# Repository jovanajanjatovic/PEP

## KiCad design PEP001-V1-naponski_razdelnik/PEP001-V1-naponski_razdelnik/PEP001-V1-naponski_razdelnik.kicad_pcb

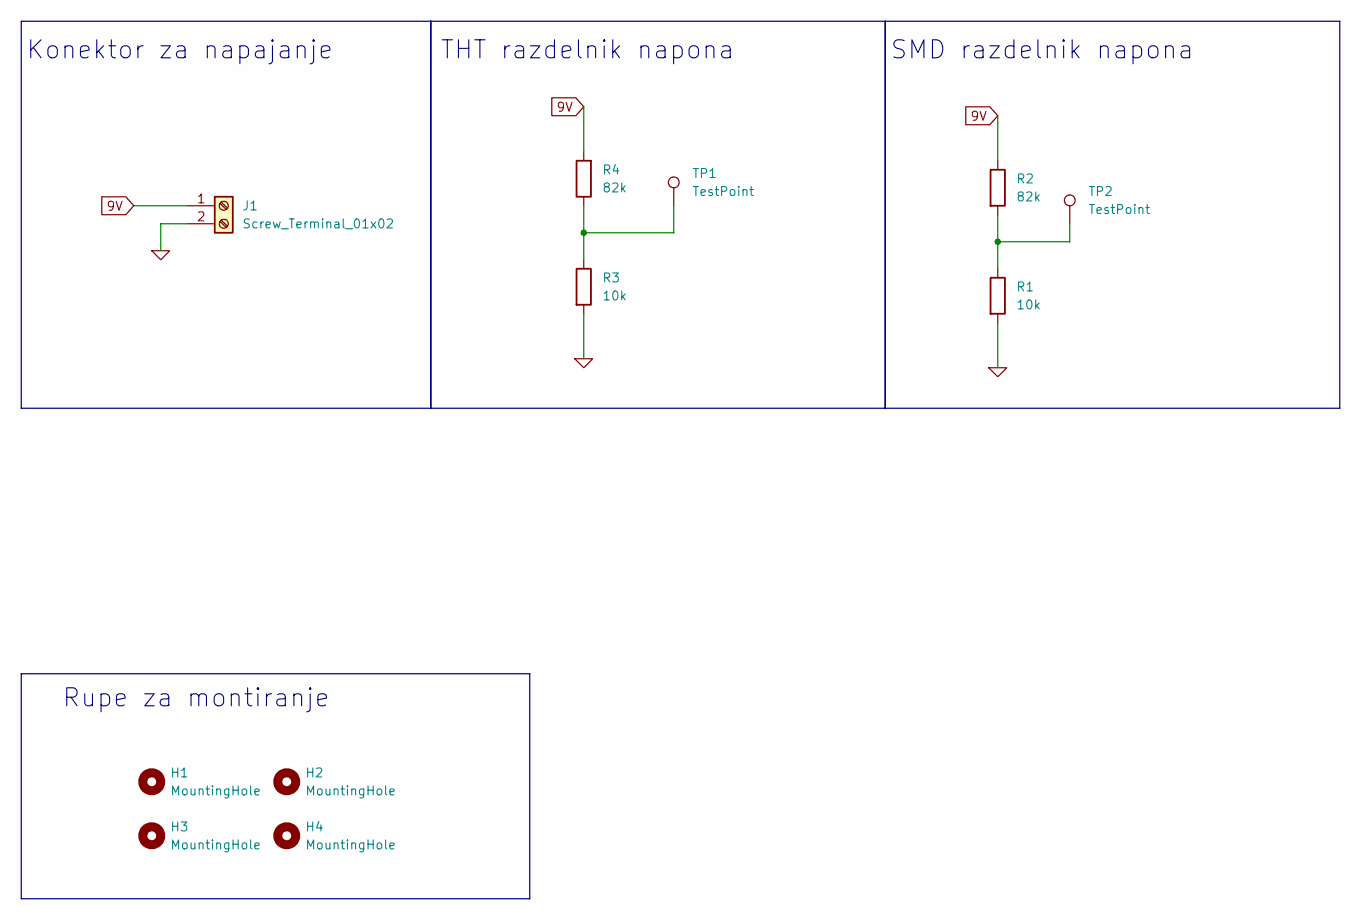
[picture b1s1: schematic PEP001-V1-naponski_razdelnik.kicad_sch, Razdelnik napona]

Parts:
H1, H2, H3, H4: MountingHole; MountingHole_3.2mm_M3_ISO14580_Pad_TopBottom
J1: Screw_Terminal_01x02; TerminalBlock_Phoenix_MKDS-1,5-2-5.08_1x02_P5.08mm_Horizont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; LCSC C3018698
R1: 10k; R_1206_3216Metric_Pad1.30x1.75mm_HandSolder; LCSC C17902
R2: 82k; R_1206_3216Metric_Pad1.30x1.75mm_HandSolder; LCSC C17979
R3: 10k; R_Axial_DIN0207_L6.3mm_D2.5mm_P15.24mm_Horizontal; LCSC C410695
R4: 82k; R_Axial_DIN0207_L6.3mm_D2.5mm_P15.24mm_Horizontal; LCSC C601724
TP1, TP2: TestPoint; TestPoint_Pad_D2.5mm

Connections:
0: J1.2, R1.2, R3.2
9V: J1.1, R2.1, R4.2
unnamed: R1.1, R2.2, TP2.1
unnamed: R3.1, R4.1, TP1.1

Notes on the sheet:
SMD razdelnik napona
Rupe za montiranje
Konektor za napajanje
THT razdelnik napona

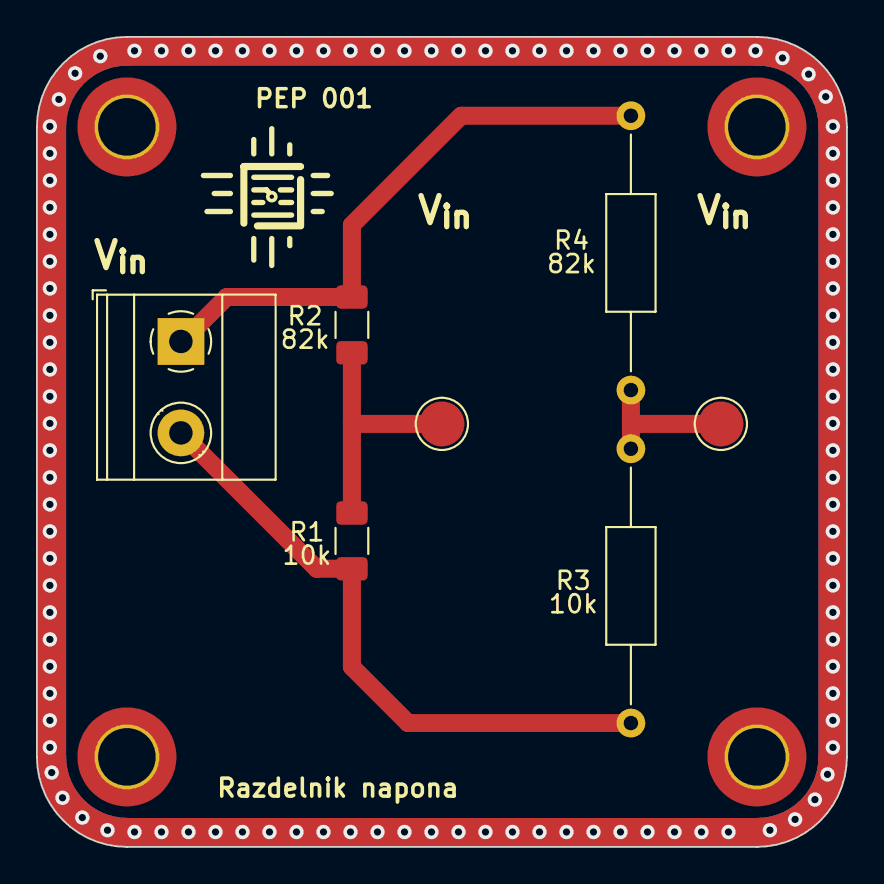
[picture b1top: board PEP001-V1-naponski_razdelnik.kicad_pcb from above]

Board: 2 copper layers, 45.0 x 45.0 mm, 11 parts (0 on the bottom side), 4 nets.

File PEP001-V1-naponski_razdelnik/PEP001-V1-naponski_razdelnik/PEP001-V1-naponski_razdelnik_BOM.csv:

"Comment","Designator","Footprint","LCSC Part Number"
"MountingHole,TestPoint","H1,H2,H3,H4,TP1,TP2","",""
"Screw_Terminal_01x02","J1","THT","C3018698"
"10k","R1","1206","C17902"
"82k","R2","1206","C17979"
"10k","R3","THT","C410695"
"82k","R4","THT","C601724"

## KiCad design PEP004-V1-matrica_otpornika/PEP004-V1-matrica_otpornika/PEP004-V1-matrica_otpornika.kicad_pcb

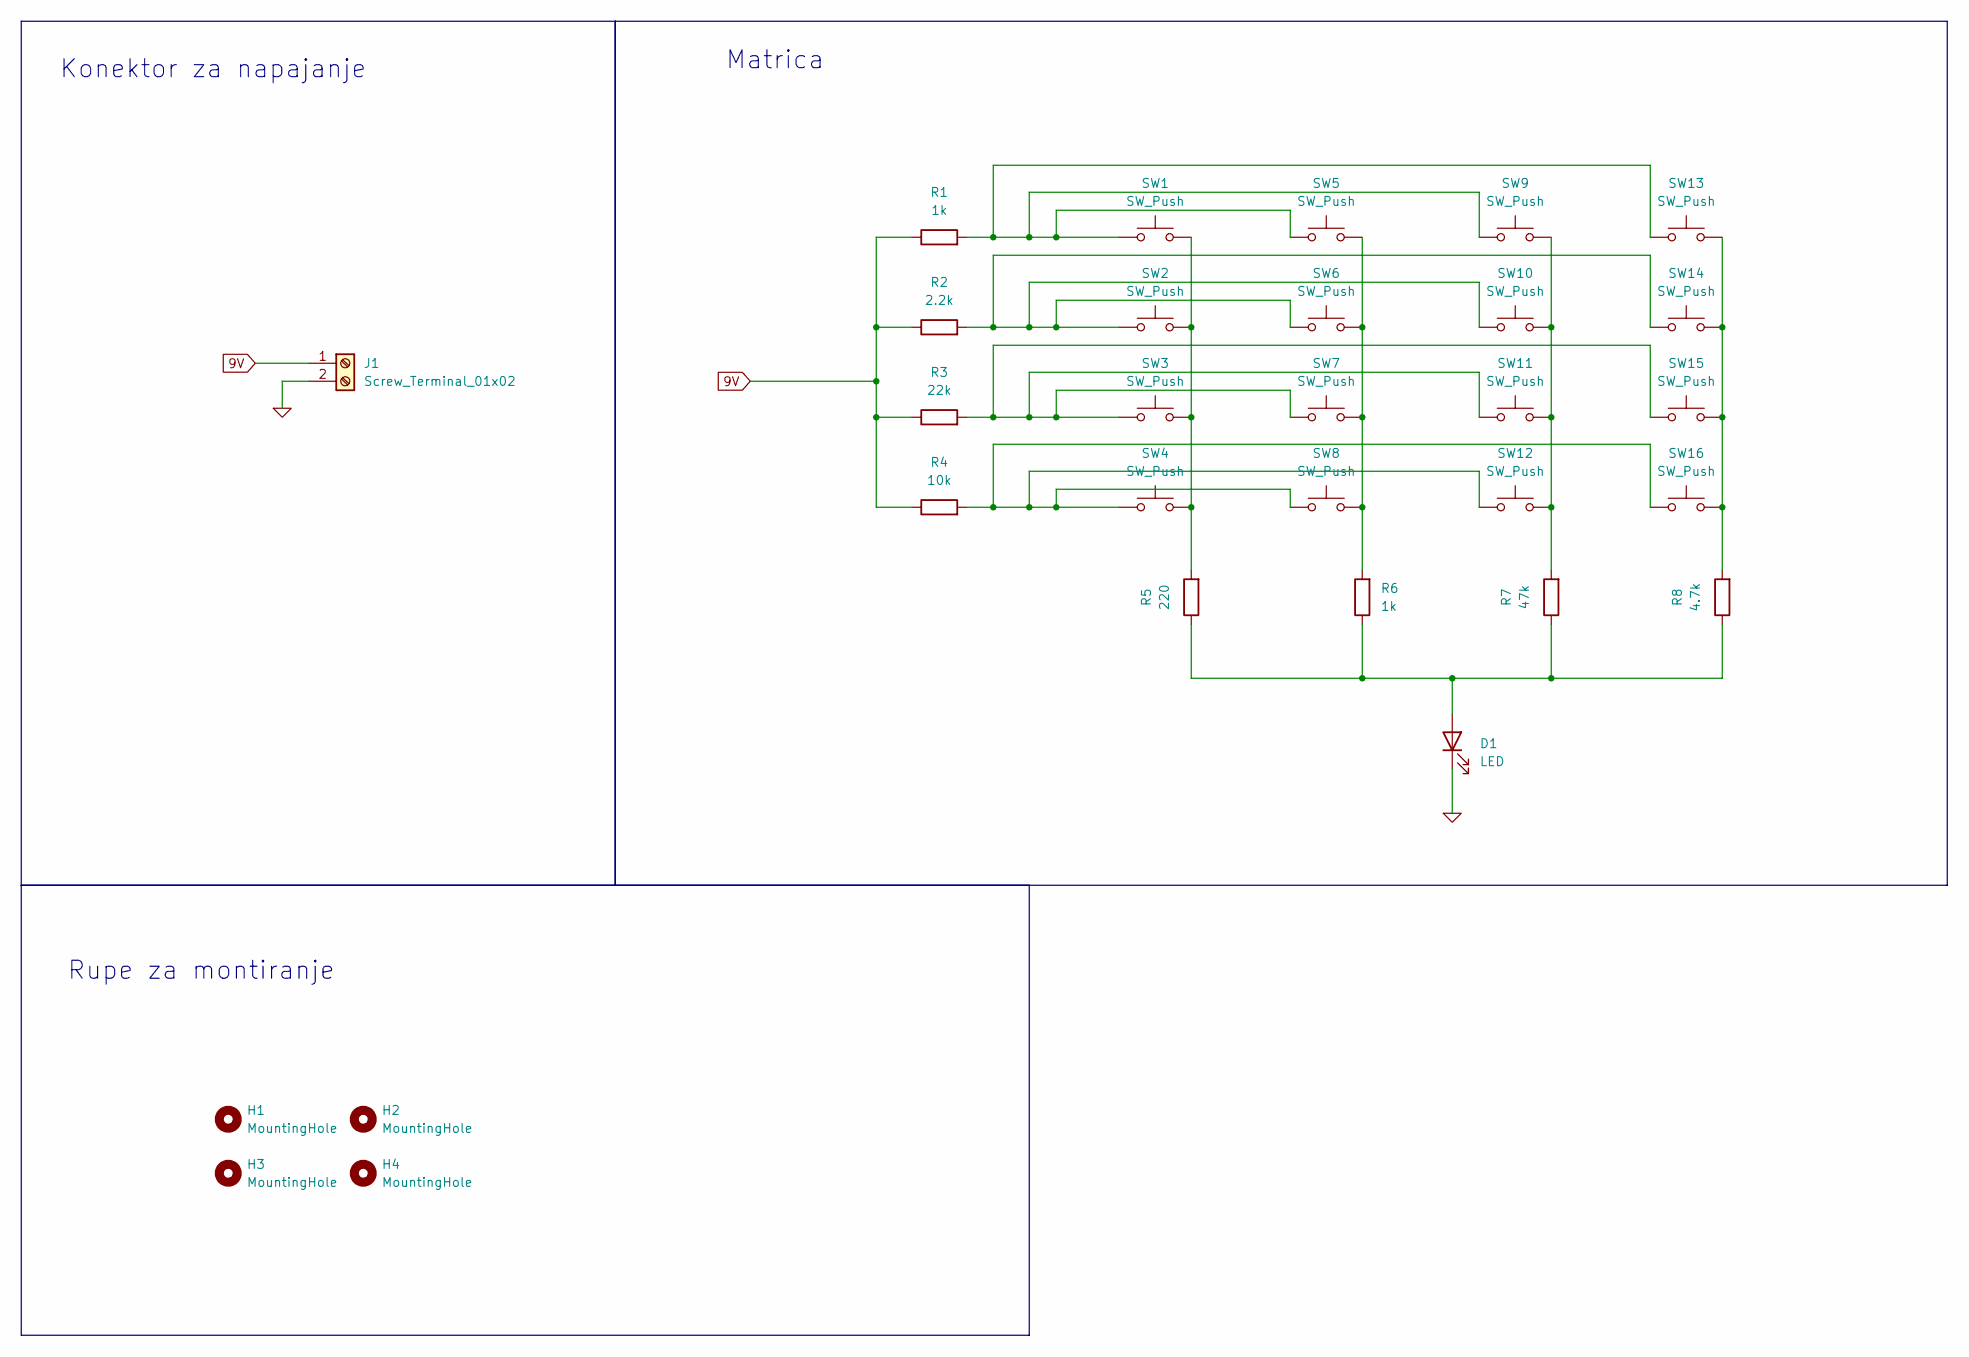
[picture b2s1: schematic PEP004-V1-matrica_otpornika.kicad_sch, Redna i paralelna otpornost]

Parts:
D1: LED; LED_0603_1608Metric_Pad1.05x0.95mm_HandSolder
H1, H2, H3, H4: MountingHole; MountingHole_3.2mm_M3_ISO14580_Pad_TopBottom
J1: Screw_Terminal_01x02; TerminalBlock_Phoenix_MKDS-1,5-2-5.08_1x02_P5.08mm_Horizont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
R1, R6: 1k; R_smd
R2: 2.2k; R_smd
R3: 22k; R_smd
R4: 10k; R_smd
R5: 220; R_smd
R7: 47k; R_smd
R8: 4.7k; R_smd
SW1, SW2, SW3, SW4, SW5, SW6, SW7, SW8, SW9, SW10, SW11, SW12, SW13, SW14, SW15, SW16: SW_Push; SW_PUSH_6mm_H4.3mm

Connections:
0: D1.1 (K), J1.2
9V: J1.1, R1.1, R2.1, R3.1, R4.1
unnamed: D1.2 (A), R5.1, R6.1, R7.1, R8.1
unnamed: R1.2, SW1.1, SW5.1, SW9.1, SW13.1
unnamed: R2.2, SW2.1, SW6.1, SW10.1, SW14.1
unnamed: R3.2, SW3.1, SW7.1, SW11.1, SW15.1
unnamed: R4.2, SW4.1, SW8.1, SW12.1, SW16.1
unnamed: R5.2, SW1.2, SW2.2, SW3.2, SW4.2
unnamed: R6.2, SW5.2, SW6.2, SW7.2, SW8.2
unnamed: R7.2, SW9.2, SW10.2, SW11.2, SW12.2
unnamed: R8.2, SW13.2, SW14.2, SW15.2, SW16.2

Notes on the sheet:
Konektor za napajanje
Rupe za montiranje
Matrica

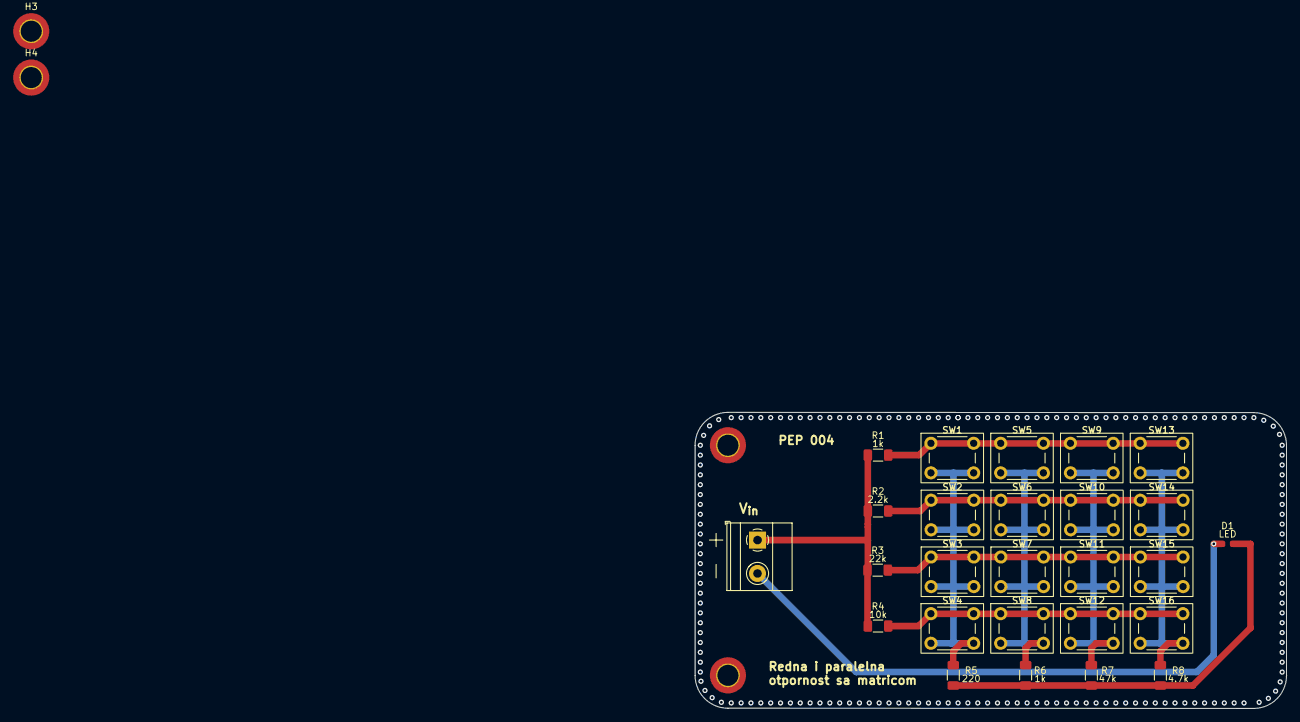
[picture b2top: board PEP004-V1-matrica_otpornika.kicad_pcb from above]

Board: 2 copper layers, 90.0 x 45.0 mm, 30 parts (0 on the bottom side), 11 nets.

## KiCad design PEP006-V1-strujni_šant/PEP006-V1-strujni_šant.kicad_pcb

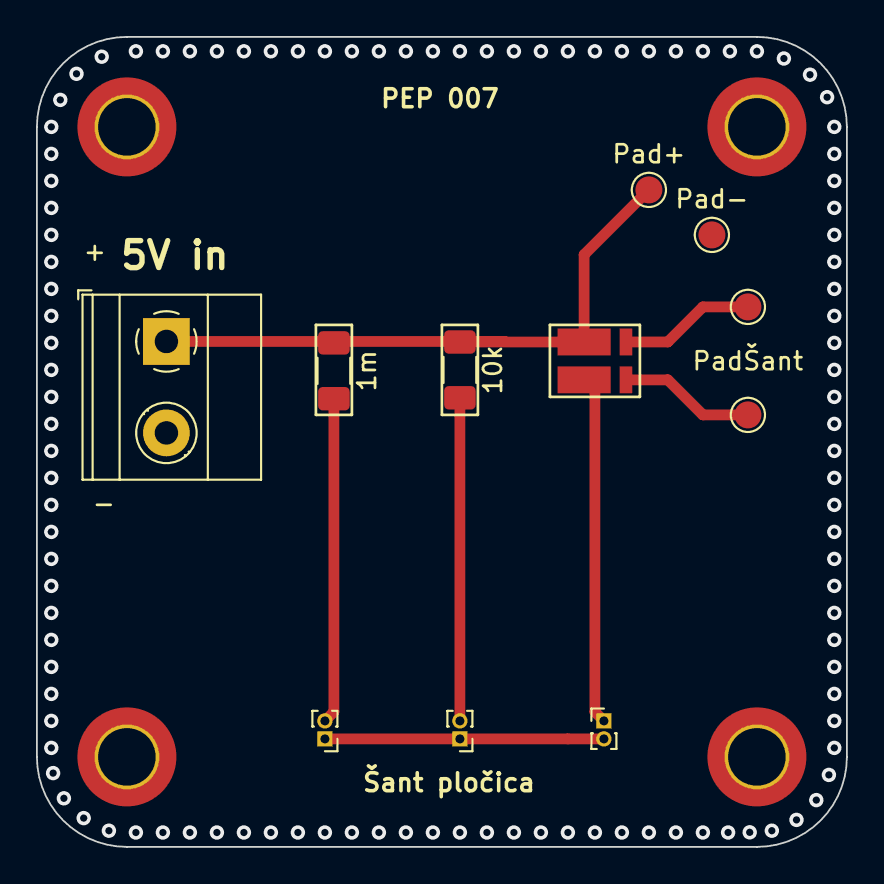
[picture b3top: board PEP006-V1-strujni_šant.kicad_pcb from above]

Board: 2 copper layers, 45.0 x 45.0 mm, 15 parts (0 on the bottom side), 7 nets.

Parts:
1m: 1m; R_1206_3216Metric_Pad1.30x1.75mm_HandSolder
10k: 10k; R_1206_3216Metric_Pad1.30x1.75mm_HandSolder
H1, H2, H3, H4: MountingHole; MountingHole_3.2mm_M3_ISO14580_Pad_TopBottom
J1: Screw_Terminal_01x02; TerminalBlock_Phoenix_MKDS-1,5-2-5.08_1x02_P5.08mm_Horizont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
J2, J3, J4: Conn_01x02_Pin; PinHeader_1x02_P1.00mm_Vertical
Pad+: TestPoint+; TestPoint_Pad_D1.5mm
Pad-: TestPoint-; TestPoint_Pad_D1.5mm
PadŠant: TestPointShunt; TestPoint_Pad_D1.5mm
R7: WSK12161; RES_WSK12161L000FEA
TP5: TestPointShunt; TestPoint_Pad_D1.5mm

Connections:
0: J1.2, J2.1, J3.1, J4.2, Pad-.1
unnamed: 1m.1, 10k.1, J1.1, Pad+.1, R7.2
unnamed: 1m.2, J2.2
unnamed: 10k.2, J3.2
unnamed: J4.1, R7.3
unnamed: R7.1, TP5.1
unnamed: PadŠant.1, R7.4

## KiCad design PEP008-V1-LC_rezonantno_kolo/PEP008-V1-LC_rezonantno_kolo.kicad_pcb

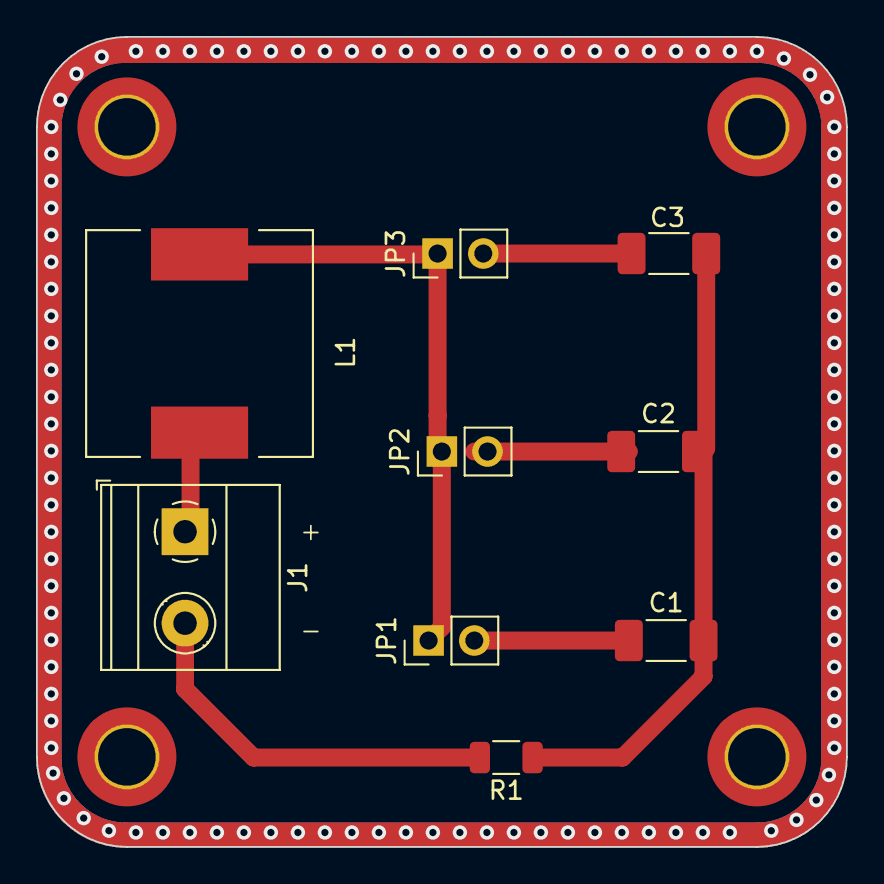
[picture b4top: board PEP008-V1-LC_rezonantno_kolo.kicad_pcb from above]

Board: 2 copper layers, 45.0 x 45.0 mm, 13 parts (0 on the bottom side), 7 nets.

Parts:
C1: 100n; C_1808_4520Metric
C2: 10n; C_1808_4520Metric
C3: 1n; C_1808_4520Metric
H1, H2, H3, H4: MountingHole; MountingHole_3.2mm_M3_ISO14580_Pad_TopBottom
J1: Screw_Terminal_01x02; TerminalBlock_Phoenix_MKDS-1,5-2-5.08_1x02_P5.08mm_Horizont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
JP1, JP2, JP3: Jumper; PinHeader_1x02_P2.54mm_Vertical
L1: 220µ; L_12x12mm_H4.5mm
R1: 100; R_1206_3216Metric

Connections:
GND: J1.2, R1.2
Input voltage: J1.1, L1.1
unnamed: C1.2, C2.2, C3.2, R1.1
unnamed: JP1.1 (A), JP2.1 (A), JP3.1 (A), L1.2
unnamed: C1.1, JP1.2 (B)
unnamed: C2.1, JP2.2 (B)
unnamed: C3.1, JP3.2 (B)

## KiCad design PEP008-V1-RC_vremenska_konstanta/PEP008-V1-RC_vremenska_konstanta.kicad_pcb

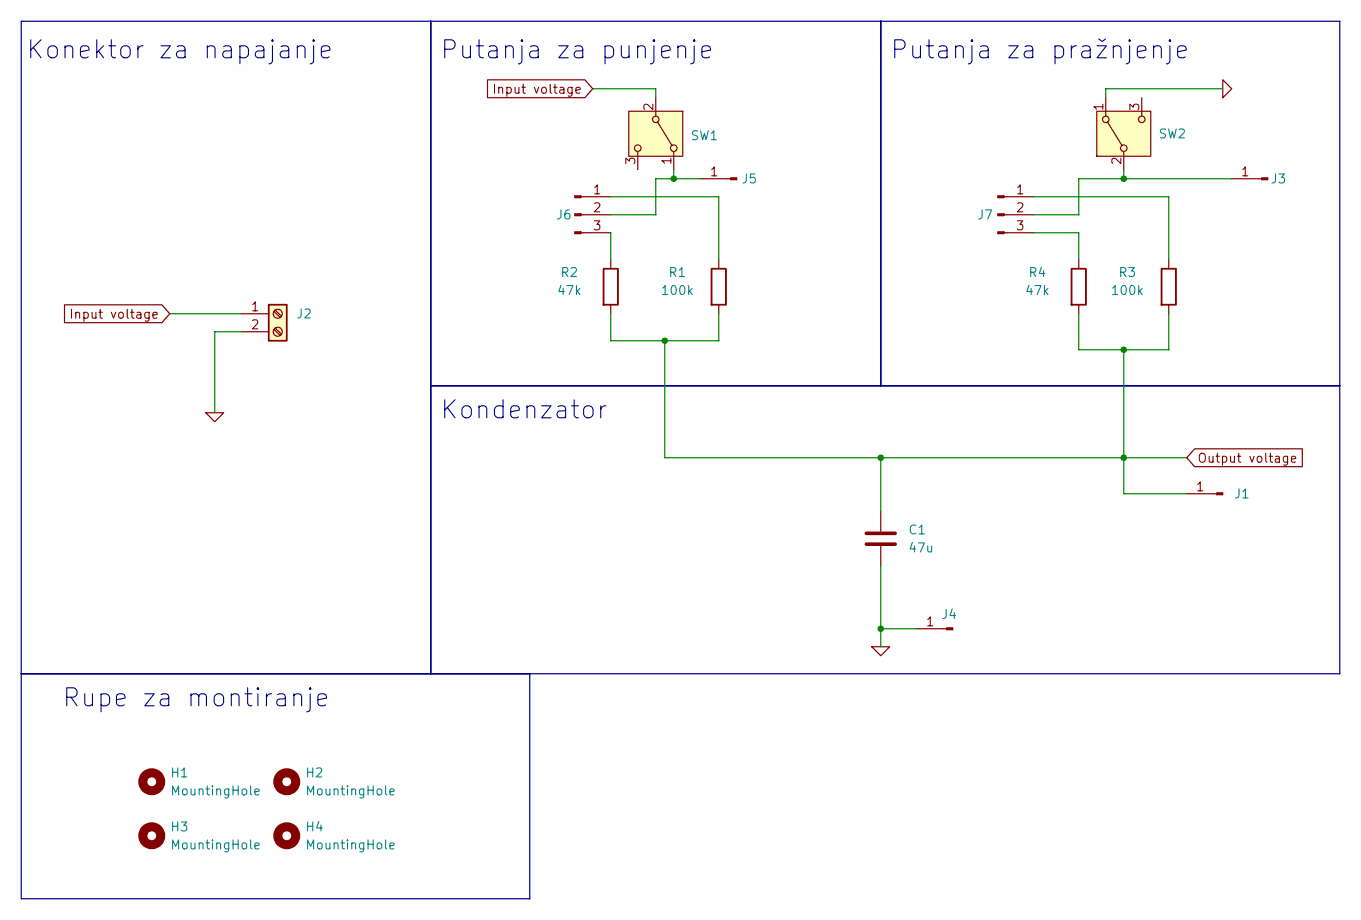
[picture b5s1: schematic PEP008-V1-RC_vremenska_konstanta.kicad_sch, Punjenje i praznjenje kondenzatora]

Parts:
C1: 47u; C_1206_3216Metric; LCSC C76659
H1, H2, H3, H4: MountingHole; MountingHole_3.2mm_M3_ISO14580_Pad_TopBottom
J1, J3, J4, J5: Conn_01x01_Pin; PinHeader_1x01_P2.54mm_Vertical
J2: Screw_Terminal_01x02; TerminalBlock_Phoenix_MKDS-1,5-2-5.08_1x02_P5.08mm_Horizont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
J6, J7: Conn_01x03_Pin; PinHeader_1x03_P2.54mm_Vertical
R1, R3: 100k; R_1206_3216Metric_Pad1.30x1.75mm_HandSolder; LCSC C17900
R2, R4: 47k; R_1206_3216Metric_Pad1.30x1.75mm_HandSolder; LCSC C25664
SW1, SW2: SW_SPDT; SW-TH_2MS1T1B1M1QES-5

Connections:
0: C1.2, J2.2, J4.1, SW2.1 (A)
Input voltage: J2.1, SW1.2 (B)
unnamed: J3.1, J7.2, SW2.2 (B)
unnamed: J5.1, J6.2, SW1.1 (A)
unnamed: J6.1, R1.1
unnamed: J6.3, R2.1
unnamed: J7.1, R3.1
unnamed: J7.3, R4.1
Output voltage: C1.1, J1.1, R1.2, R2.2, R3.2, R4.2

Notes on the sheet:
Rupe za montiranje
Kondenzator
Konektor za napajanje
Putanja za pražnjenje
Putanja za punjenje

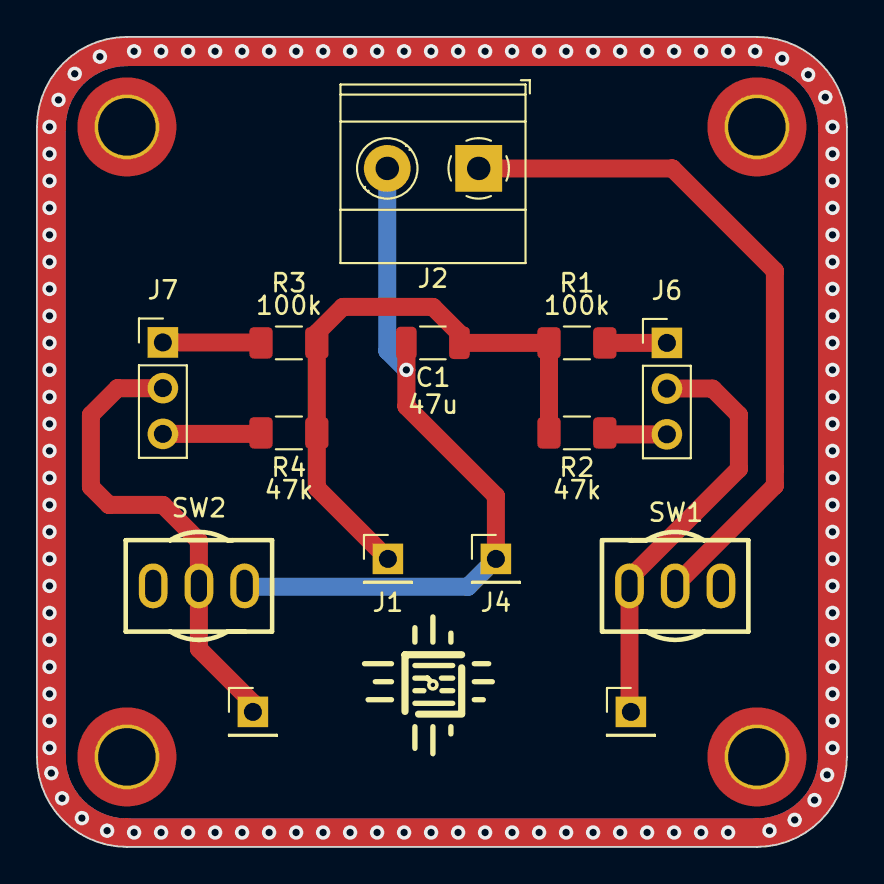
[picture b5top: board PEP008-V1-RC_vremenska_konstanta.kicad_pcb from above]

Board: 2 copper layers, 45.0 x 45.0 mm, 18 parts (0 on the bottom side), 9 nets.

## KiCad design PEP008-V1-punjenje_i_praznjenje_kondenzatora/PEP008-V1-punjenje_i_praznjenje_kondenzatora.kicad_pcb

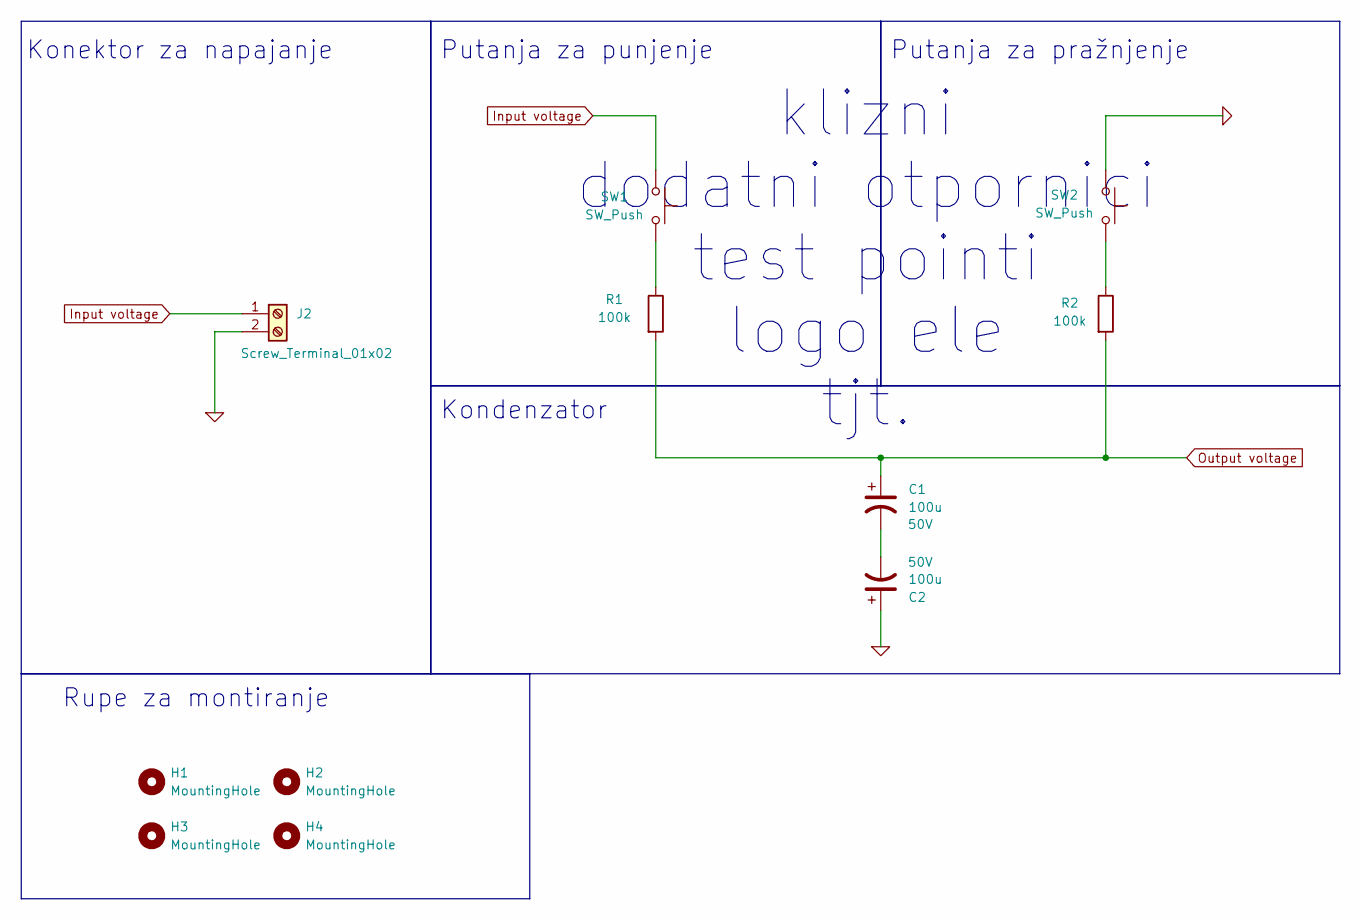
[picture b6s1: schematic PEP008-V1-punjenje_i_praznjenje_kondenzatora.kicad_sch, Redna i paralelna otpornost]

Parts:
C1, C2: 100u; CP_Radial_D8.0mm_P3.50mm; Voltage 50V
H1, H2, H3, H4: MountingHole; MountingHole_3.2mm_M3_ISO14580_Pad_TopBottom
J2: Screw_Terminal_01x02; TerminalBlock_Phoenix_MKDS-1,5-2-5.08_1x02_P5.08mm_Horizont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
R1, R2: 100k; R_1206_3216Metric_Pad1.30x1.75mm_HandSolder
SW1, SW2: SW_Push; SW_PUSH_6mm_H4.3mm

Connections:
0: C2.1, J2.2, SW2.1
Input voltage: J2.1, SW1.1
unnamed: C1.2, C2.2
unnamed: R1.1, SW1.2
unnamed 4: R2.1, SW2.2; also elsewhere on the board
Output voltage: C1.1, R1.2, R2.2; also elsewhere on the board

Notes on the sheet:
Putanja za pražnjenje
Rupe za montiranje
Kondenzator
Konektor za napajanje
Putanja za punjenje
klizni dodatni otpornici test pointi logo ele tjt.

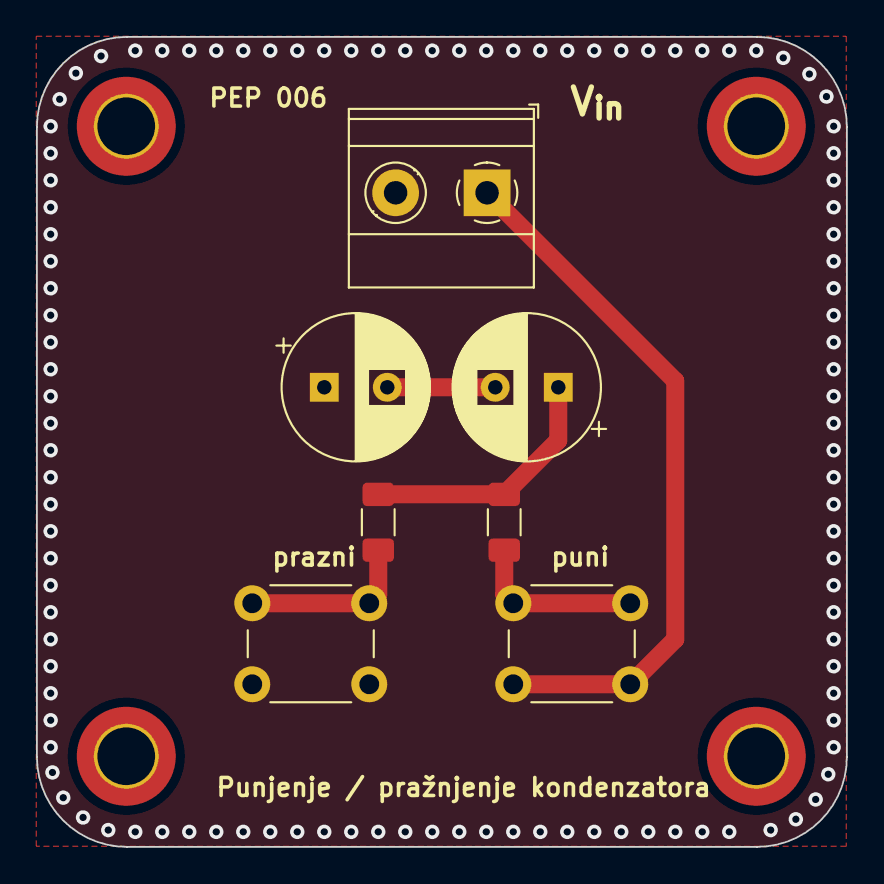
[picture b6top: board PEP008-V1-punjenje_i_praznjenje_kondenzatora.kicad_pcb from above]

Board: 2 copper layers, 45.0 x 45.0 mm, 11 parts (0 on the bottom side), 6 nets.

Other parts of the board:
R6: 100k; R_1206_3216Metric_Pad1.30x1.75mm_HandSolder

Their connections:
unnamed 4: R6.1; also elsewhere on the board
Output voltage: R6.2; also elsewhere on the board

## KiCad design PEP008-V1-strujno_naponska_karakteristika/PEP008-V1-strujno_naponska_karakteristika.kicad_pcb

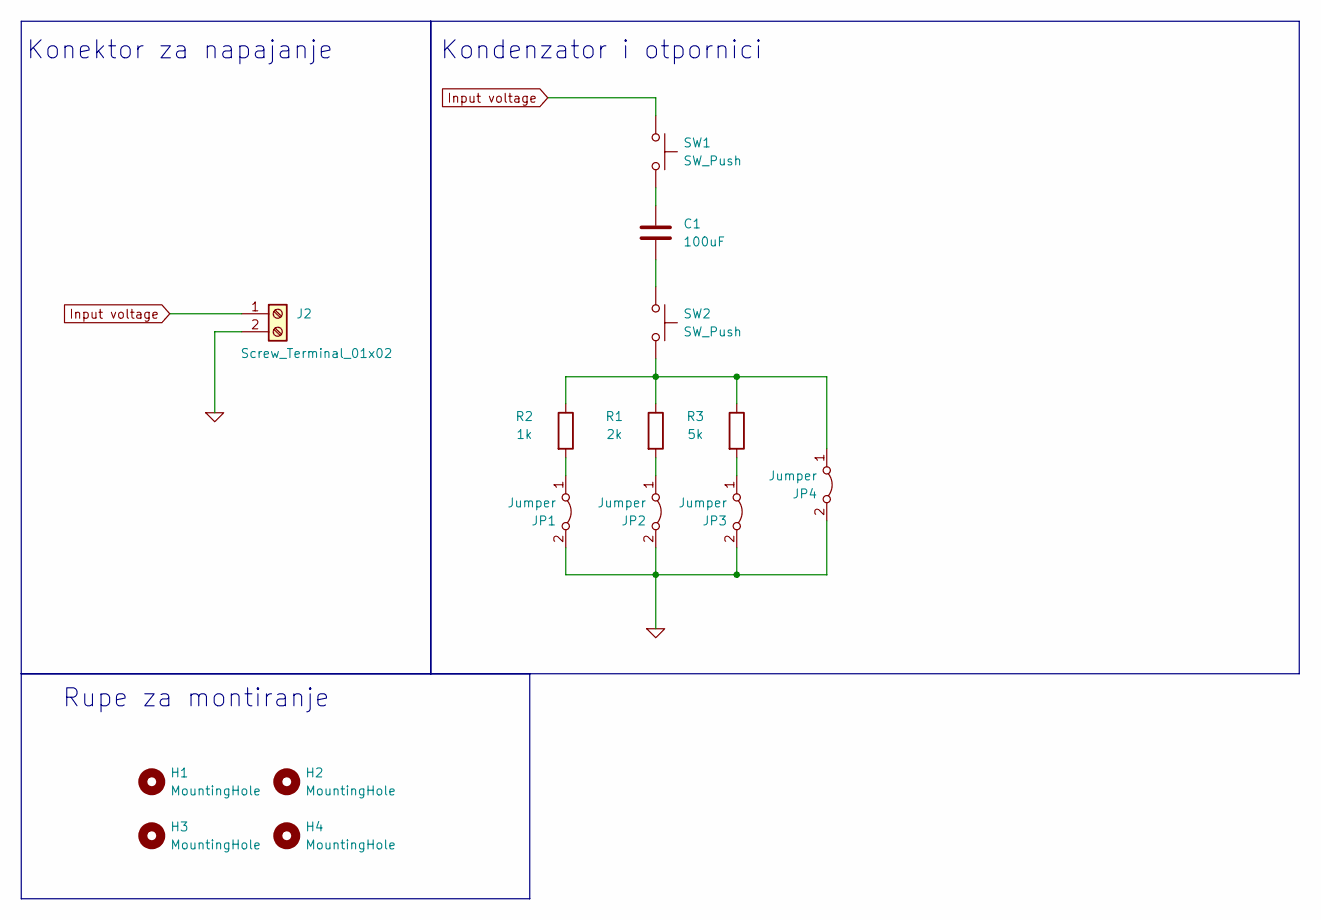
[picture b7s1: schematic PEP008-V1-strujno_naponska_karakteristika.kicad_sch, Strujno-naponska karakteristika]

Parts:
C1: 100uF; C_Disc_D5.0mm_W2.5mm_P2.50mm
H1, H2, H3, H4: MountingHole; MountingHole_3.2mm_M3_ISO14580_Pad_TopBottom
J2: Screw_Terminal_01x02; TerminalBlock_Phoenix_MKDS-1,5-2-5.08_1x02_P5.08mm_Horizont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
JP1, JP2, JP3, JP4: Jumper; PinHeader_1x02_P2.54mm_Vertical
R1: 2k; R_1206_3216Metric_Pad1.30x1.75mm_HandSolder
R2: 1k; R_1206_3216Metric_Pad1.30x1.75mm_HandSolder
R3: 5k; R_1206_3216Metric_Pad1.30x1.75mm_HandSolder
SW1, SW2: SW_Push; SW_PUSH_6mm_H4.3mm

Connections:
0: J2.2, JP1.2 (B), JP2.2 (B), JP3.2 (B), JP4.2 (B)
Input voltage: J2.1, SW1.1
unnamed: C1.1, SW1.2
unnamed: C1.2, SW2.1
unnamed: JP1.1 (A), R2.2
unnamed: JP2.1 (A), R1.2
unnamed: JP3.1 (A), R3.2
unnamed: JP4.1 (A), R1.1, R2.1, R3.1, SW2.2

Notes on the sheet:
Rupe za montiranje
Konektor za napajanje
Kondenzator i otpornici

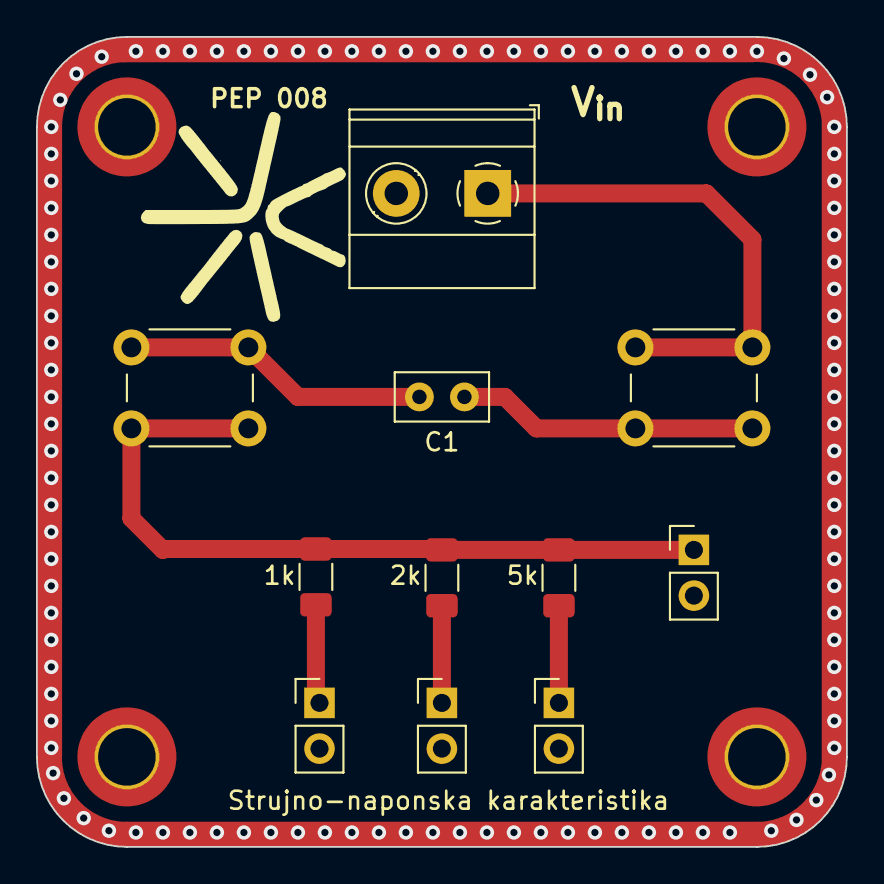
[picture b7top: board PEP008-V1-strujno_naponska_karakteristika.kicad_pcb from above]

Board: 2 copper layers, 45.0 x 45.0 mm, 15 parts (0 on the bottom side), 8 nets.
